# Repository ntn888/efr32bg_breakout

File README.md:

# E104-BT53A3 (EFR32BG22C224F512GM32 module) breakout

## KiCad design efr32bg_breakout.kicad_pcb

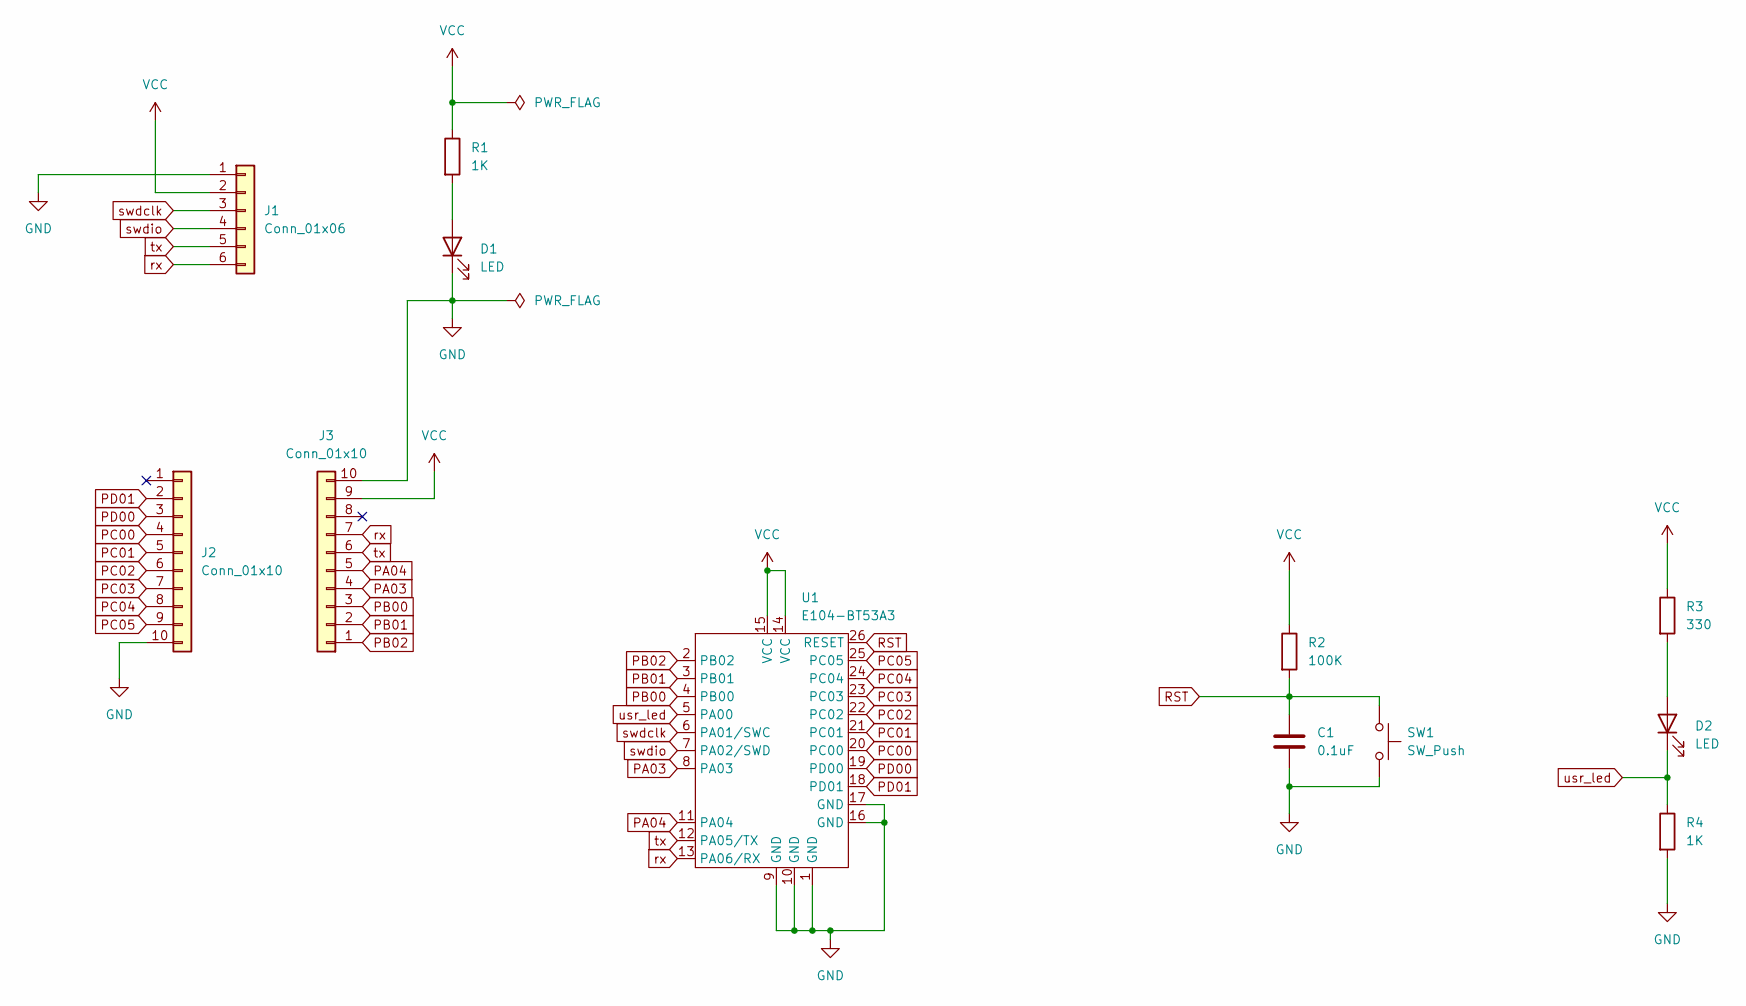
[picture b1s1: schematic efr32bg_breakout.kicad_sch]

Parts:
C1: 0.1uF; C_0402_1005Metric
D1, D2: LED; LED_0603_1608Metric
J1: Conn_01x06; PinHeader_1x06_P2.54mm_Horizontal
J2, J3: Conn_01x10; PinHeader_1x10_P2.54mm_Vertical
R1, R4: 1K; R_0402_1005Metric
R2: 100K; R_0402_1005Metric
R3: 330; R_0402_1005Metric
SW1: SW_Push; SW_SPST_TS-1088-AR02016
U1: E104-BT53A3; E104-BT53A3_module

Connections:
GND: C1.2, D1.1 (K), J1.1, J2.10, J3.10, R4.2, SW1.2, U1.1 (GND), U1.9 (GND), U1.10 (GND), U1.16 (GND), U1.17 (GND)
unnamed: D1.2 (A), R1.2
unnamed: D2.2 (A), R3.2
PA03: J3.4, U1.8 (PA03)
PA04: J3.5, U1.11 (PA04)
PB00: J3.3, U1.4 (PB00)
PB01: J3.2, U1.3 (PB01)
PB02: J3.1, U1.2 (PB02)
PC00: J2.4, U1.20 (PC00)
PC01: J2.5, U1.21 (PC01)
PC02: J2.6, U1.22 (PC02)
PC03: J2.7, U1.23 (PC03)
PC04: J2.8, U1.24 (PC04)
PC05: J2.9, U1.25 (PC05)
PD00: J2.3, U1.19 (PD00)
PD01: J2.2, U1.18 (PD01)
RST: C1.1, R2.2, SW1.1, U1.26 (RESET)
VCC: J1.2, J3.9, R1.1, R2.1, R3.1, U1.14 (VCC), U1.15 (VCC)
rx: J1.6, J3.7, U1.13 (PA06/RX)
swdclk: J1.3, U1.6 (PA01/SWC)
swdio: J1.4, U1.7 (PA02/SWD)
tx: J1.5, J3.6, U1.12 (PA05/TX)
usr_led: D2.1 (K), R4.1, U1.5 (PA00)

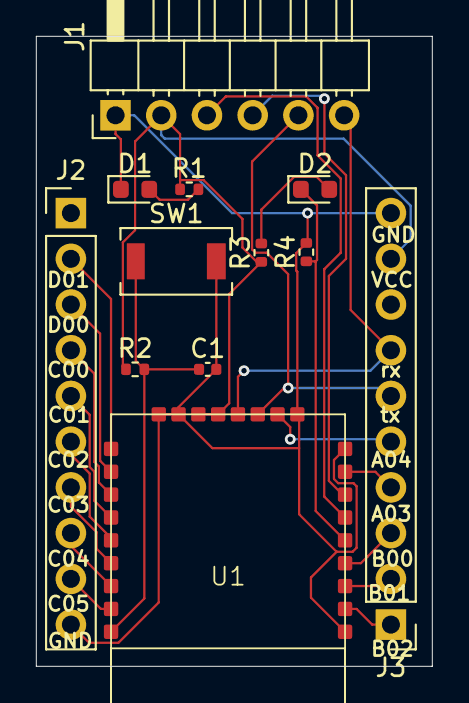
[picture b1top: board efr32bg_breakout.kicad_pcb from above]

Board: 2 copper layers, 22.0 x 35.0 mm, 12 parts (0 on the bottom side), 23 nets.

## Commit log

2025-08-03 use 0603 leds
2025-08-03 final bom output
2025-08-08 collect pcba files
